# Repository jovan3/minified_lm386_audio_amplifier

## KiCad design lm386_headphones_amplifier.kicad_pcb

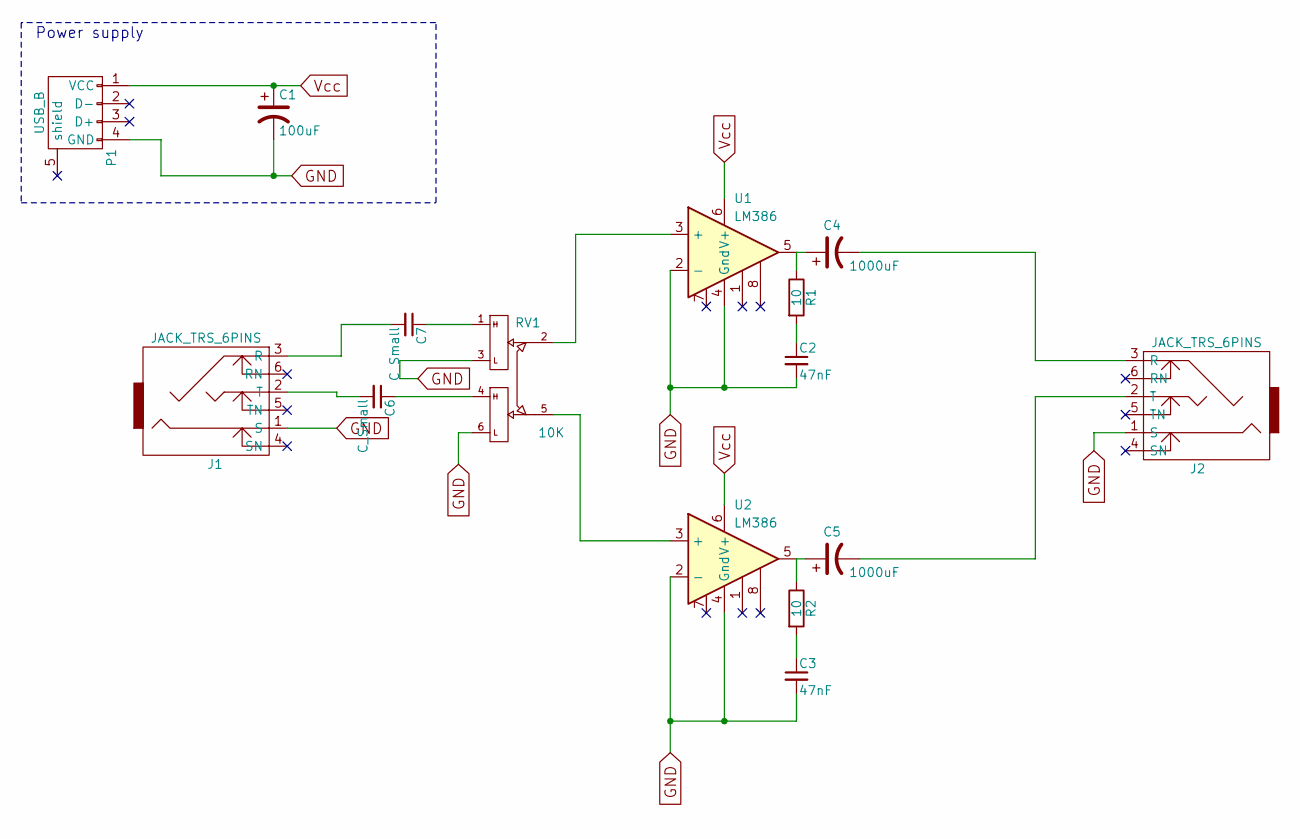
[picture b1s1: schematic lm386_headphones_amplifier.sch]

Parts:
C1: 100uF; C_Radial_D5_L11_P2
C2, C3: 47nF; C_Disc_D3_P2.5
C4, C5: 1000uF; C_Radial_D10_L13_P5
C6, C7: C_Small; C_Disc_D3_P2.5
J1, J2: JACK_TRS_6PINS; Tayda_3.5mm_stereo_TRS_jack_A-853
P1: USB_B
R1, R2: 10; Resistor_Horizontal_RM10mm
RV1: 10K; Potentiometer_Alps-RK16-double
U1, U2: LM386; DIP-8_W7.62mm

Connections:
GND: C1.2, C2.2, C3.2, J1.1 (S), J2.1 (S), P1.4 (GND), RV1.3, RV1.6, U1.2 (-), U1.4 (Gnd), U2.2 (-), U2.4 (Gnd)
unnamed: C2.1, R1.2
unnamed: C3.1, R2.2
unnamed: C4.1, R1.1, U1.5
unnamed: C4.2, J2.3 (R)
unnamed: C5.1, R2.1, U2.5
unnamed: C5.2, J2.2 (T)
unnamed: C6.1, RV1.4
unnamed: C6.2, J1.2 (T)
unnamed: C7.1, RV1.1
unnamed: C7.2, J1.3 (R)
unnamed: RV1.2, U1.3 (+)
unnamed: RV1.5, U2.3 (+)
Vcc: C1.1, P1.1 (VCC), U1.6 (V+), U2.6 (V+)

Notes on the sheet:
Power supply

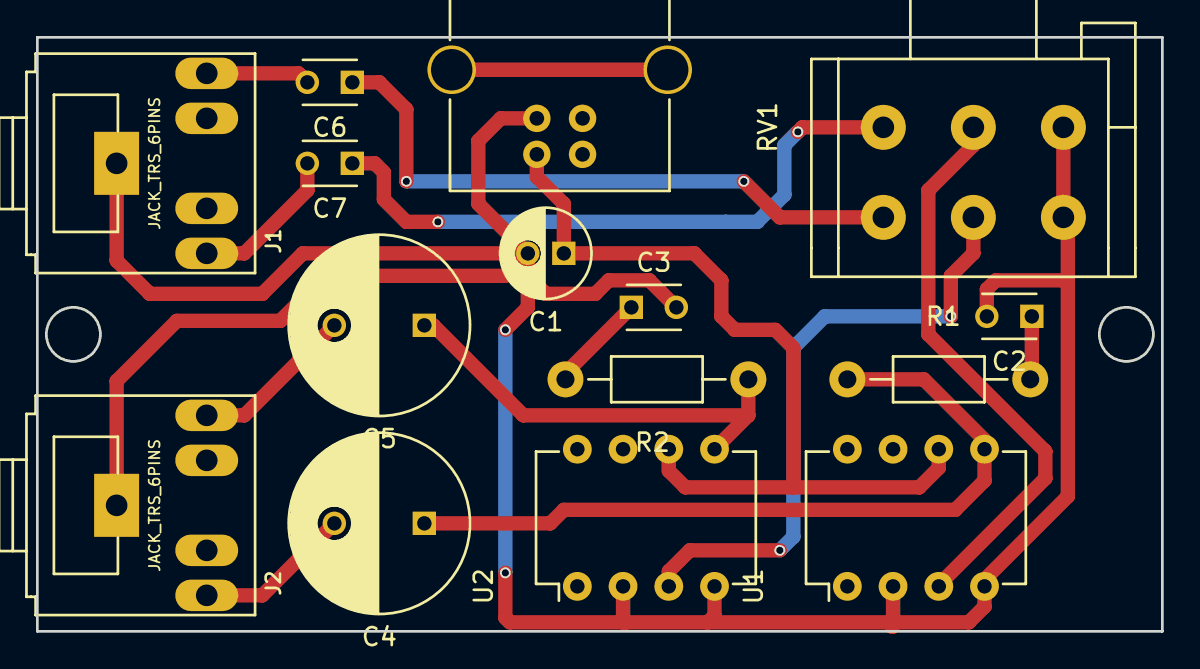
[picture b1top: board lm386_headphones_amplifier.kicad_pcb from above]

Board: 2 copper layers, 62.5 x 33.0 mm, 15 parts (0 on the bottom side), 14 nets.

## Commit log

2018-05-06 add 100 nF input jack capacitors. Wire the components in pcbnew
2018-05-08 use large usb type b connector. move stuff around a bit
